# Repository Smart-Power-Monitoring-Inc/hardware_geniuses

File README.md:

# hardware_section
### TO-DO
*  Setup Hostspot with root node
*  Connect PI to root's hotspot
*  Make requests withing them

```c++
#define SERVER_PATH "http://10.192.18.110:3000/summary/current?accountId="
#define VOLTAGE_PATH "http://10.192.18.110:3000/summary/" + accountId + "/voltage"
String accountId = "62cc2c675065faa3815663ec";
```
<p>The variables above are the most important for data transfer between devices and the server. When you set it up on
the Raspberry  PI, configure your own static ip and replace it here, or use the IP defined here as the static IP </p>

```c++
bool isRoot = true;
```
<p> For the accound Id, you have to write it here manually for now.<p>
<p> Remember to set 'isRoot' to false when uploading to other nodes and true when uploading to the root note <p>

## Start Sequence
1. Start node 1
2. Connect smart phone to HOTSPOT set up by node. If you want to run this with the smart hub, post all the data to the loopback address of the smart hub '127.0.0.1' or the smart hubs IP address
3. Power OTher nodes and wait for a 200 status code in the serial monitor
4. Start the backend server 
```sh
nodemon index.js
```

5. Before demonstrating, run the app and everything that day. Errors may occur in the backend. Just restart the server so the database updates its values

# Kindly report Errors to me

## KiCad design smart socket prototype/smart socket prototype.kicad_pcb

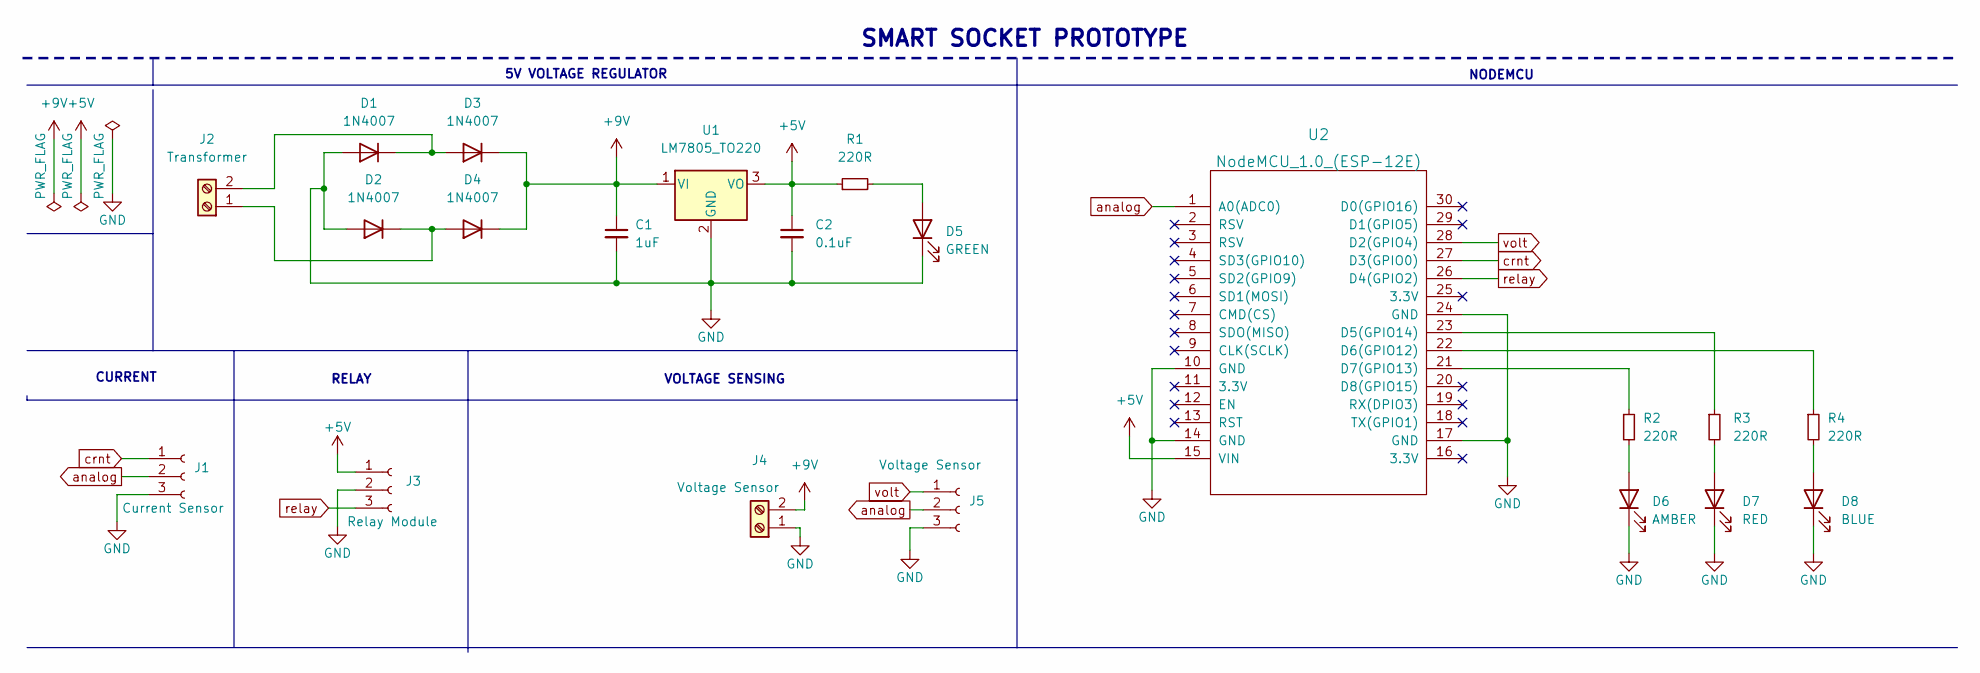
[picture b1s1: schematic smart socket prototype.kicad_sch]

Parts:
C1: 1uF; CP_Radial_D4.0mm_P2.00mm
C2: 0.1uF; CP_Radial_D4.0mm_P2.00mm
D1, D2, D3, D4: 1N4007; D_DO-41_SOD81_P10.16mm_Horizontal
D5: GREEN; LED_D5.0mm
D6: AMBER; LED_D5.0mm
D7: RED; LED_D5.0mm
D8: BLUE; LED_D5.0mm
J1: Current Sensor; PinSocket_1x03_P2.54mm_Vertical
J2: Transformer; TerminalBlock_bornier-2_P5.08mm
J3: Relay Module; PinSocket_1x03_P2.54mm_Vertical
J4: Voltage Sensor; TerminalBlock_bornier-2_P5.08mm
J5: Voltage Sensor; PinSocket_1x03_P2.54mm_Vertical
R1, R2, R3, R4: 220R; R_Axial_DIN0204_L3.6mm_D1.6mm_P5.08mm_Horizontal
U1: LM7805_TO220; TO-220-3_Vertical
U2: NodeMCU_1.0_(ESP-12E); NodeMCU1.0(12-E)

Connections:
+5V: C2.1, J3.1, R1.1, U1.3 (VO), U2.15 (VIN)
+9V: C1.1, D3.1 (K), D4.1 (K), J4.2, U1.1 (VI)
GND: C1.2, C2.2, D1.2 (A), D2.2 (A), D5.1 (K), D6.1 (K), D7.1 (K), D8.1 (K), J1.3, J3.2, J4.1, J5.3, U1.2 (GND), U2.10 (GND), U2.14 (GND), U2.17 (GND), U2.24 (GND)
unnamed: D1.1 (K), D3.2 (A), J2.2
unnamed: D2.1 (K), D4.2 (A), J2.1
unnamed: D5.2 (A), R1.2
unnamed: D6.2 (A), R2.2
unnamed: D7.2 (A), R3.2
unnamed: D8.2 (A), R4.2
unnamed: R2.1, U2.21 (D7(GPIO13))
unnamed: R3.1, U2.23 (D5(GPIO14))
unnamed: R4.1, U2.22 (D6(GPIO12))
analog: J1.2, J5.2, U2.1 (A0(ADC0))
crnt: J1.1, U2.27 (D3(GPIO0))
relay: J3.3, U2.26 (D4(GPIO2))
volt: J5.1, U2.28 (D2(GPIO4))

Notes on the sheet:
CURRENT
5V VOLTAGE REGULATOR
SMART SOCKET PROTOTYPE
RELAY
NODEMCU
VOLTAGE SENSING

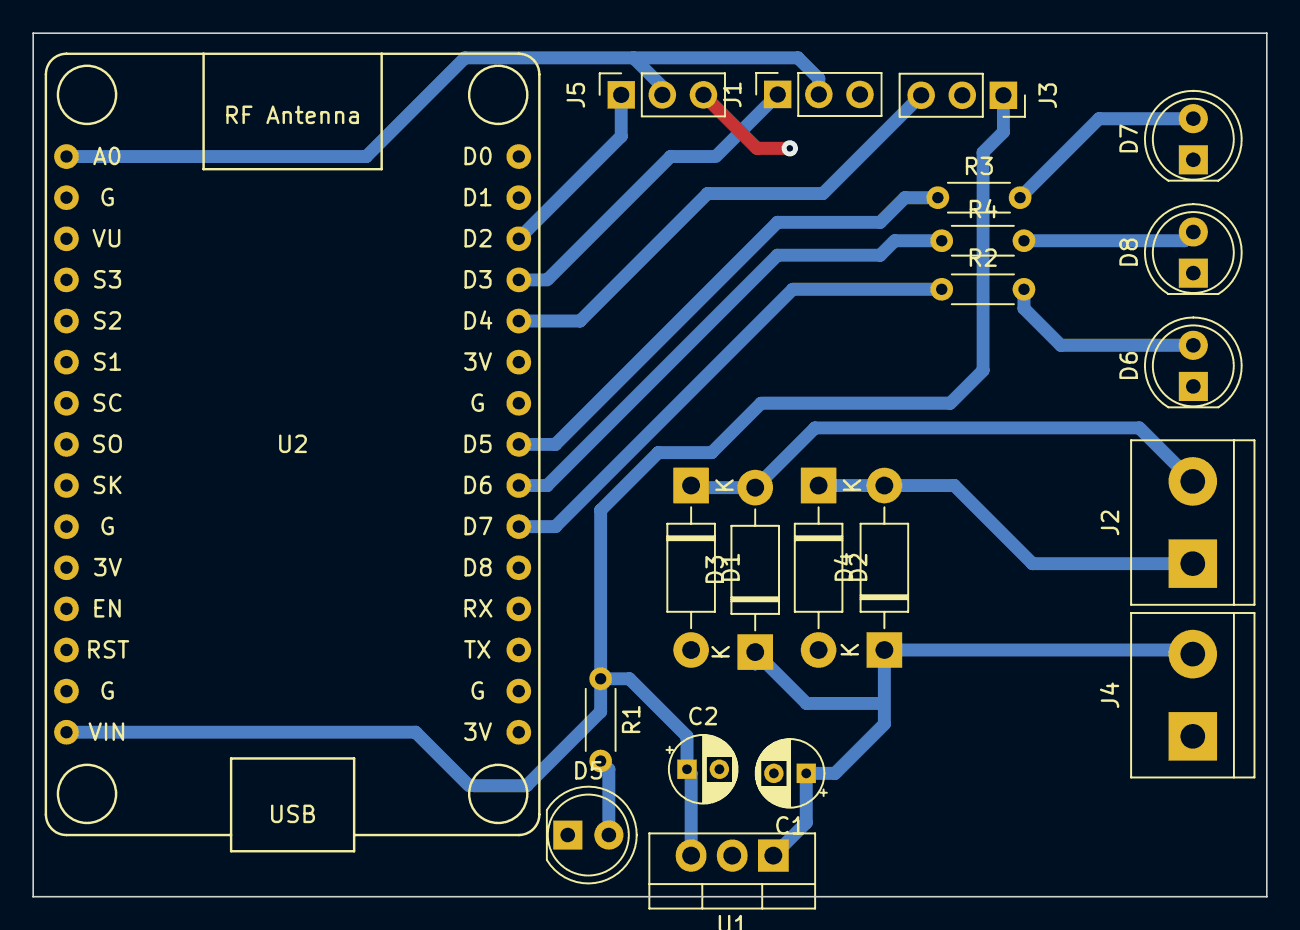
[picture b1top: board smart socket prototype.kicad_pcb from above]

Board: 2 copper layers, 76.2 x 53.3 mm, 21 parts (0 on the bottom side), 16 nets.

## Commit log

2022-05-12 Arduino code dir
2022-05-12 functions
2022-05-30 Add WiFi libraries to the code
2022-05-30 Add functions for connecting ESP32 UDP request
2022-05-31 Include code for sending data to the smarthub
2022-05-31 Last commit on office pc
2022-06-29 Add the first hardware design prototype
2022-06-30 new org
2022-07-01 created hotspot
2022-07-01 post to server
2022-07-20 backup
2022-07-24 updates to the readme
